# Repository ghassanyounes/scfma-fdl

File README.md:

# scfma-fdl
Seattle Community Fridge Mutual Aid Project - Food Donation Logger

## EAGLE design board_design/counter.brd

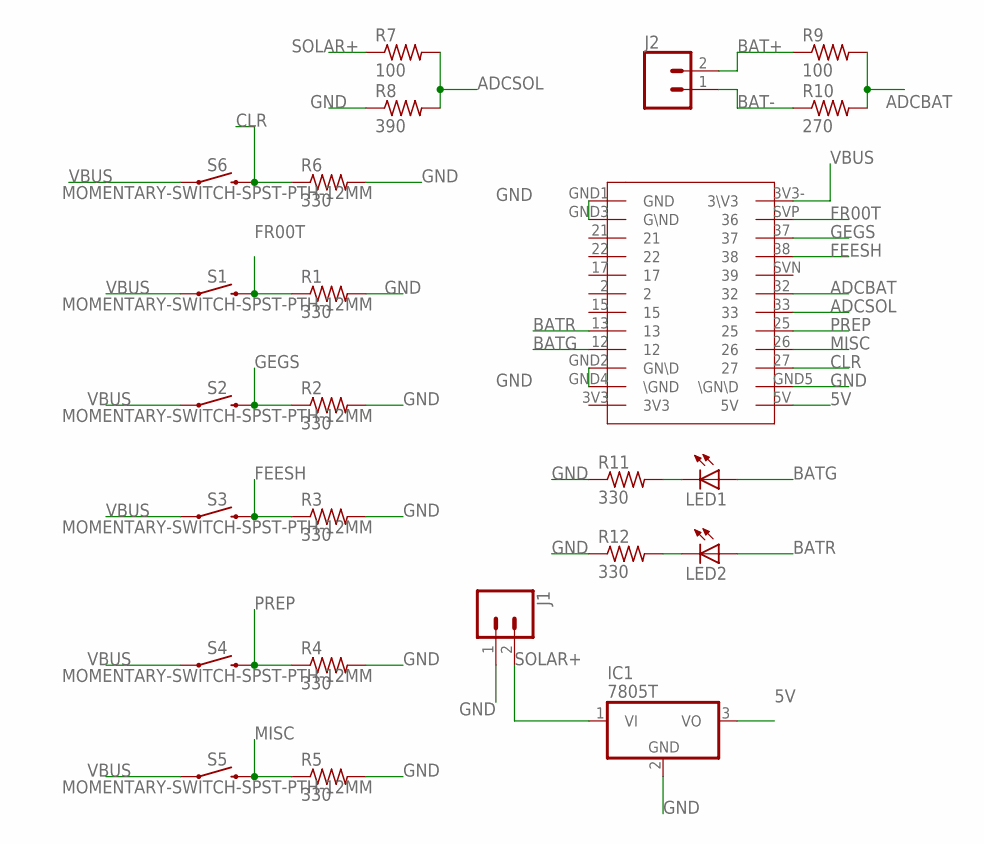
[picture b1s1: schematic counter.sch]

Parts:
IC1: 7805T; TO220H
J1, J2: CONN_02; 1X02
LED1, LED2: LED3MM
R1, R2, R3, R4, R5, R6, R11, R12: 330; 0204/7
R7, R9: 100; 0204/7
R8: 390; 0204/7
R10: 270; 0204/7
S1, S2, S3, S4, S5, S6: MOMENTARY-SWITCH-SPST-PTH-12MM; TACTILE_SWITCH_PTH_12MM
U$1: TTGO-4MB; ESP32-TTGO-TDISPLAY

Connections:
5V: IC1.3 (VO), U$1.5V
ADCBAT: R9.2, R10.2, U$1.32
ADCSOL: R7.2, R8.2, U$1.33
BAT+: J2.2, R9.1
BAT-: J2.1, R10.1
BATG: LED1.A, U$1.12
BATR: LED2.A, U$1.13
CLR: R6.1, S6.3 (2), U$1.27
FEESH: R3.1, S3.3 (2), U$1.38
FR00T: R1.1, S1.3 (2), U$1.SVP (36)
GEGS: R2.1, S2.3 (2), U$1.37
GND: IC1.2 (GND), J1.1, R1.2, R2.2, R3.2, R4.2, R5.2, R6.2, R8.1, R11.1, R12.1, U$1.GND1 (GND), U$1.GND2 (GN\D), U$1.GND3 (G\ND), U$1.GND4 (\GND), U$1.GND5 (\GN\D)
MISC: R5.1, S5.3 (2), U$1.26
unnamed: LED1.K (C), R11.2
unnamed: LED2.K (C), R12.2
PREP: R4.1, S4.3 (2), U$1.25
SOLAR+: IC1.1 (VI), J1.2, R7.1
VBUS: S1.1, S2.1, S3.1, S4.1, S5.1, S6.1, U$1.3V3- (3\V3)

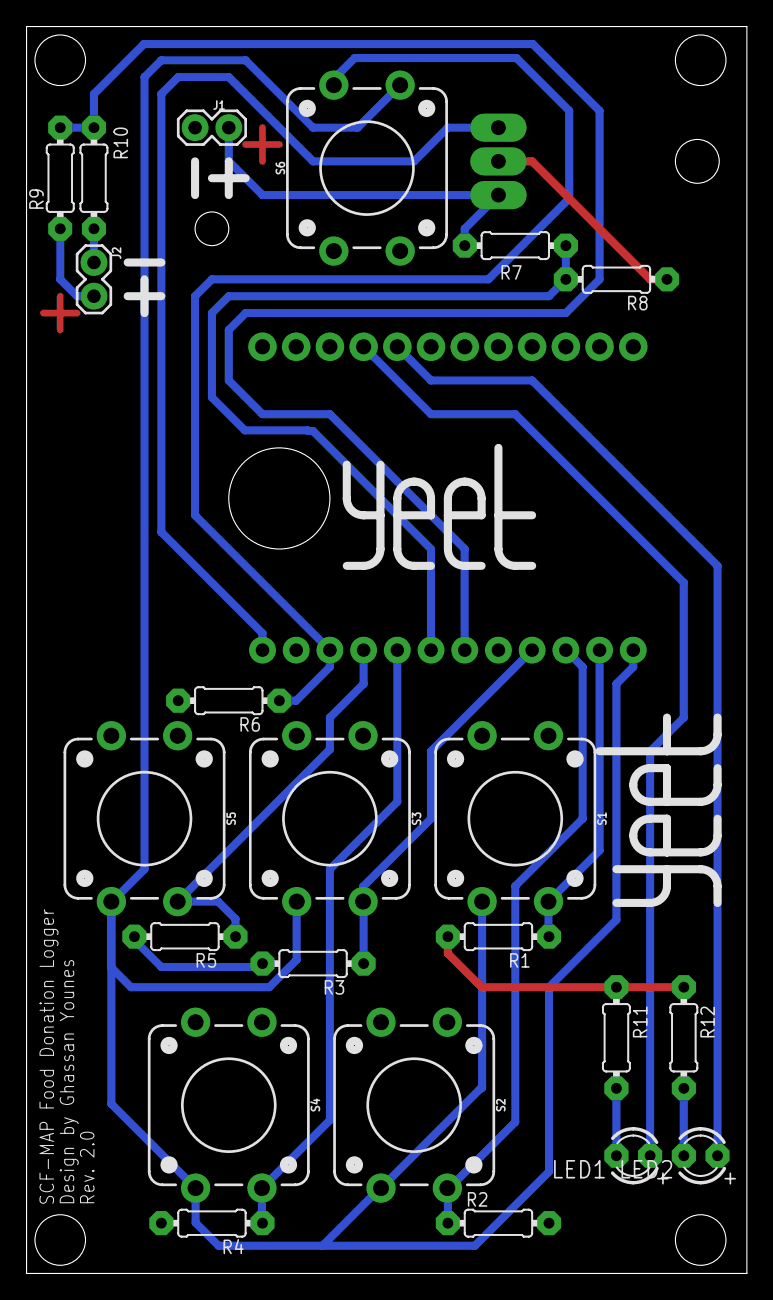
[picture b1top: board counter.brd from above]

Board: 2 copper layers, 54.3 x 94.0 mm, 24 parts (1 on the bottom side), 18 nets.

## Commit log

2021-07-31 Added Folders and Files
    Also updated the .gitignore to ignore eagle backup files
2021-07-31 added to do list to code comment
2021-07-31 Commenting code
2021-07-31 forgot to change variable names lmao
2021-07-31 constant names
2021-08-01 implemented some sleep functionality - not fully tested yet
2021-08-01 Board update
2021-08-02 Implemented sleep and wakeup
    Only misc and prep meals actually wake it up
2021-08-02 Sleep mostly working plus EEPROM storage
2021-08-03 Modified board not to have ADC on the boot pins (woops)
2021-08-03 Renamed variables, improved hard reset
2021-08-03 Even better hard reset, sleep mode adjustments
2021-08-03 couple changes to board

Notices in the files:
parts and their libraries:
SparkFun-Connectors: Licensing: Creative Commons ShareAlike 4.0 International - https://creativecommons.org/licenses/by-sa/4.0
